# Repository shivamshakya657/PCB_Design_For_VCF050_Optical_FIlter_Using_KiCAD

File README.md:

# PCB_Design-_For_VCF050_Optical_FIlter_Using_KiCAD
In this project, My task is to design PCB for electronics control of Optical Bandpass filter using KiCAD from scratch.

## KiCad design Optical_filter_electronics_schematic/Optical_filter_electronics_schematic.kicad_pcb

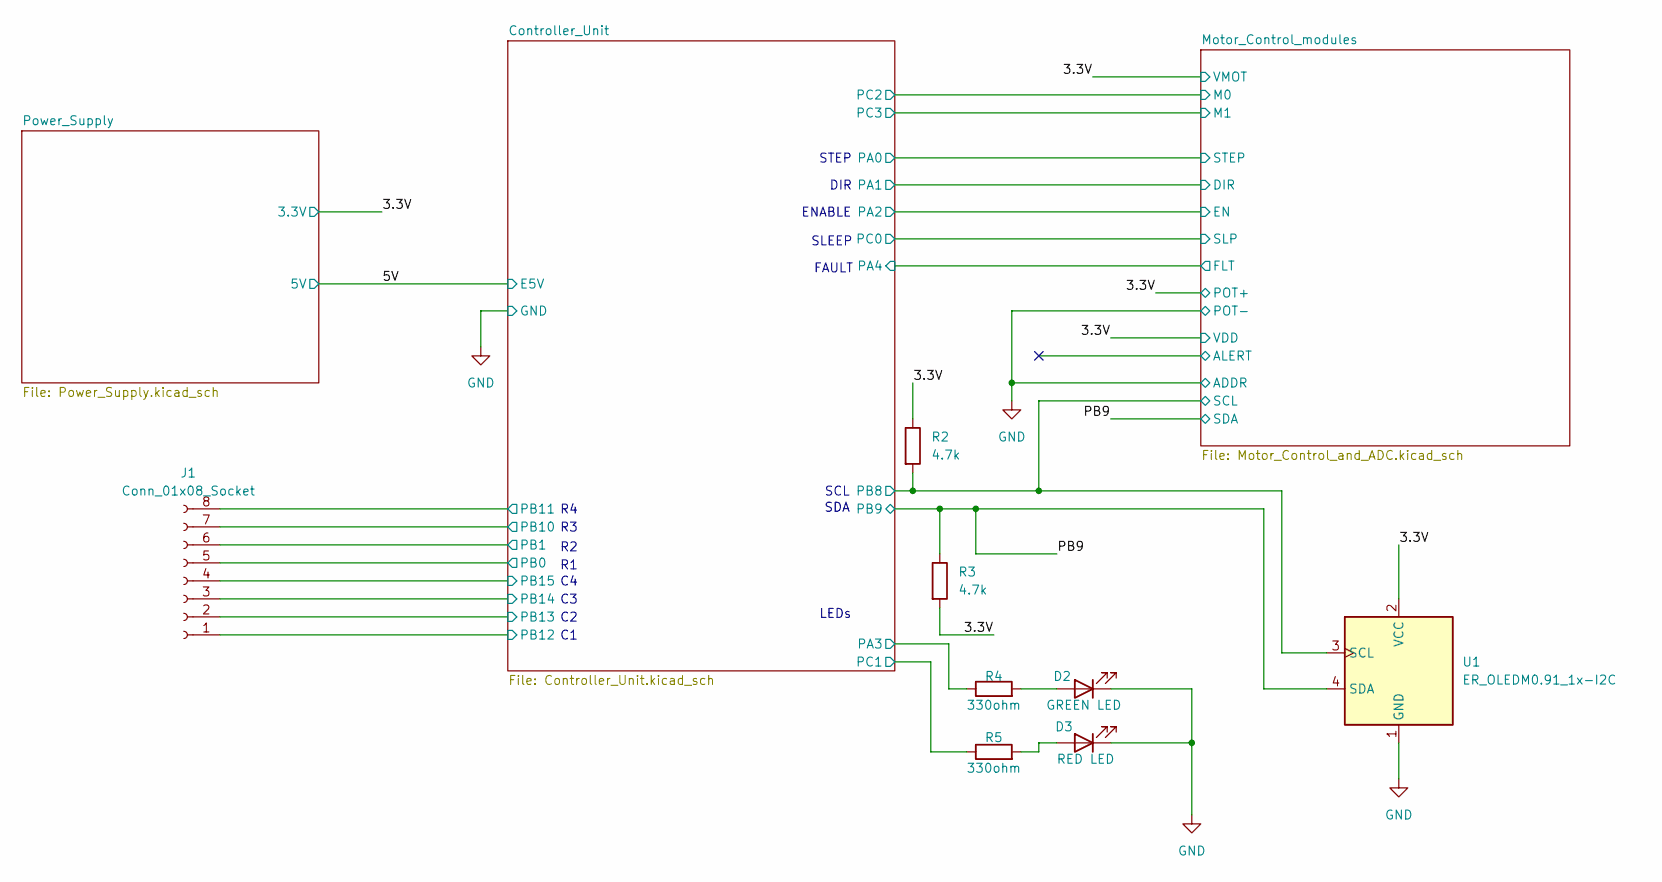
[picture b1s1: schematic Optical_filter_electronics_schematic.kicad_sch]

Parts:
D2: GREEN LED; LED_D5.0mm
D3: RED LED; LED_D5.0mm
J1: Conn_01x08_Socket; Keypad_4x4_footprint
R2, R3: 4.7k; R_0805_2012Metric_Pad1.20x1.40mm_HandSolder
R4, R5: 330ohm; R_0805_2012Metric_Pad1.20x1.40mm_HandSolder
U1: ER_OLEDM0.91_1x-I2C; 128x64OLED_custom_footprint

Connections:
/3.3V: R2.1, R3.2, U1.2 (VCC); also elsewhere on the board
/Controller_Unit/PA3: R4.1; also elsewhere on the board
/Controller_Unit/PB0: J1.5; also elsewhere on the board
/Controller_Unit/PB1: J1.6; also elsewhere on the board
/Controller_Unit/PB8: R2.2, U1.3 (SCL); also elsewhere on the board
/Controller_Unit/PB10: J1.7; also elsewhere on the board
/Controller_Unit/PB11: J1.8; also elsewhere on the board
/Controller_Unit/PB12: J1.1; also elsewhere on the board
/Controller_Unit/PB13: J1.2; also elsewhere on the board
/Controller_Unit/PB14: J1.3; also elsewhere on the board
/Controller_Unit/PB15: J1.4; also elsewhere on the board
/Controller_Unit/PC1: R5.1; also elsewhere on the board
/PB9: R3.1, U1.4 (SDA); also elsewhere on the board
GND: D2.1 (K), D3.1 (K), U1.1 (GND); also elsewhere on the board
unnamed: D2.2 (A), R4.2
unnamed: D3.2 (A), R5.2

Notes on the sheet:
SLEEP
STEP
FAULT
LEDs
ENABLE
SDA
SCL
DIR

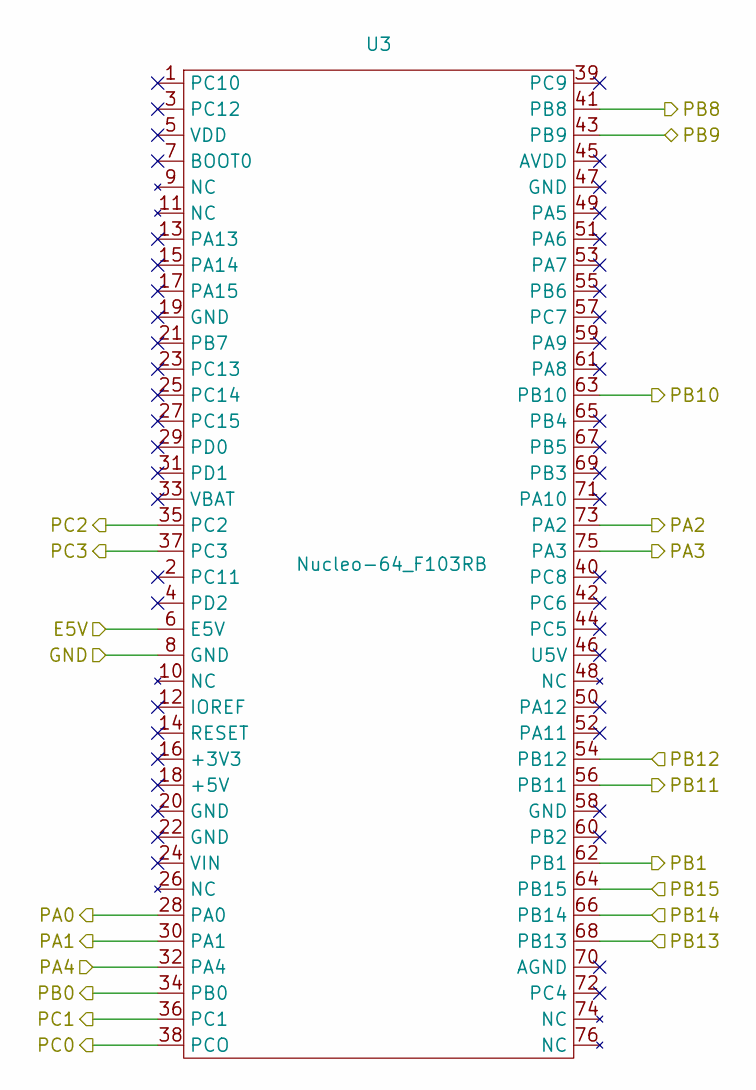
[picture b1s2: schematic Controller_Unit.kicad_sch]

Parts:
U3: Nucleo-64_F103RB; STM32_footprint

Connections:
/5V: U3.6 (E5V); also elsewhere on the board
/Controller_Unit/PA0: U3.28 (PA0); also elsewhere on the board
/Controller_Unit/PA1: U3.30 (PA1); also elsewhere on the board
/Controller_Unit/PA2: U3.73 (PA2); also elsewhere on the board
/Controller_Unit/PA3: U3.75 (PA3); also elsewhere on the board
/Controller_Unit/PA4: U3.32 (PA4); also elsewhere on the board
/Controller_Unit/PB0: U3.34 (PB0); also elsewhere on the board
/Controller_Unit/PB1: U3.62 (PB1); also elsewhere on the board
/Controller_Unit/PB8: U3.41 (PB8); also elsewhere on the board
/Controller_Unit/PB10: U3.63 (PB10); also elsewhere on the board
/Controller_Unit/PB11: U3.56 (PB11); also elsewhere on the board
/Controller_Unit/PB12: U3.54 (PB12); also elsewhere on the board
/Controller_Unit/PB13: U3.68 (PB13); also elsewhere on the board
/Controller_Unit/PB14: U3.66 (PB14); also elsewhere on the board
/Controller_Unit/PB15: U3.64 (PB15); also elsewhere on the board
/Controller_Unit/PC0: U3.38 (PCO); also elsewhere on the board
/Controller_Unit/PC1: U3.36 (PC1); also elsewhere on the board
/Controller_Unit/PC2: U3.35 (PC2); also elsewhere on the board
/Controller_Unit/PC3: U3.37 (PC3); also elsewhere on the board
/PB9: U3.43 (PB9); also elsewhere on the board
GND: U3.8 (GND); also elsewhere on the board

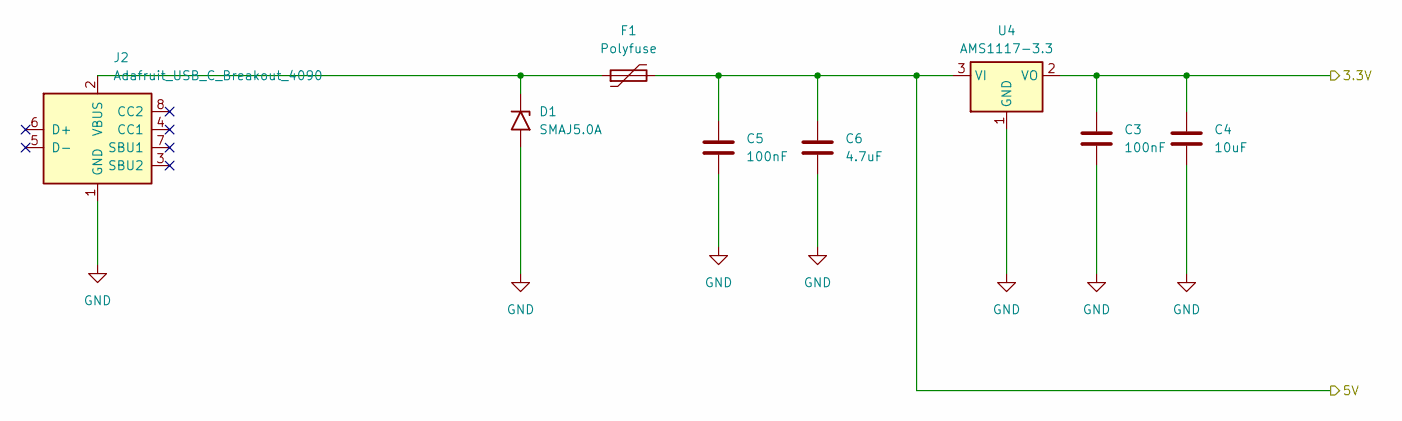
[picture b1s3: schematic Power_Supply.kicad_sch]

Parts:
C3, C5: 100nF; C_0805_2012Metric_Pad1.18x1.45mm_HandSolder
C4: 10uF; C_1206_3216Metric_Pad1.33x1.80mm_HandSolder
C6: 4.7uF; C_1206_3216Metric_Pad1.33x1.80mm_HandSolder
D1: SMAJ5.0A; D_SMA
F1: Polyfuse; Fuse_1812_4532Metric_Pad1.30x3.40mm_HandSolder
J2: Adafruit_USB_C_Breakout_4090
U4: AMS1117-3.3; 3V3_Regulator_Footprint

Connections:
/3.3V: C3.1, C4.1, U4.2 (VO); also elsewhere on the board
/5V: C5.1, C6.1, F1.2, U4.3 (VI); also elsewhere on the board
GND: C3.2, C4.2, C5.2, C6.2, D1.2 (A2), J2.1 (GND), U4.1 (GND); also elsewhere on the board
unnamed: D1.1 (A1), F1.1, J2.2 (VBUS)

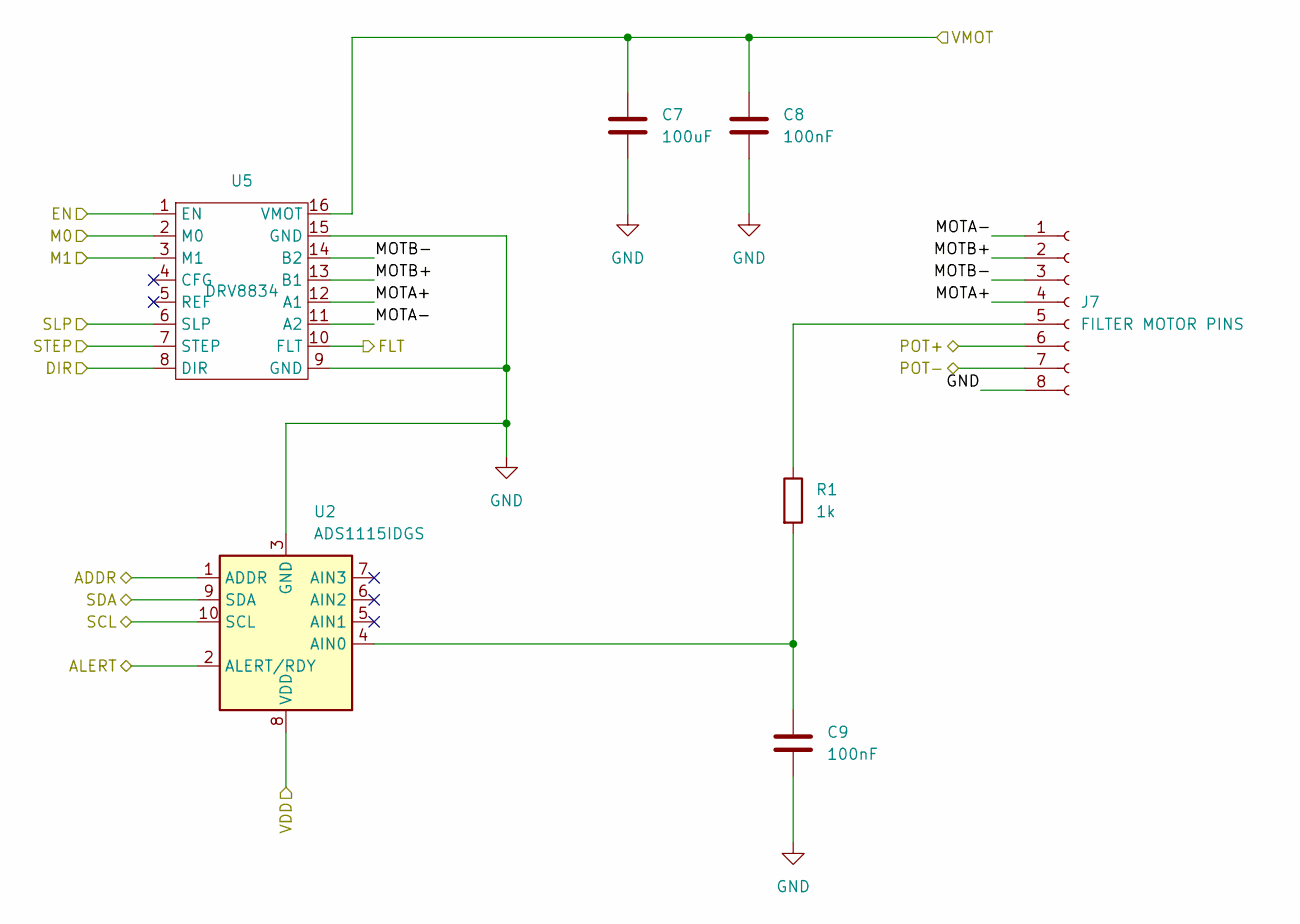
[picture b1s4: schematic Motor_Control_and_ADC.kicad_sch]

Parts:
C7: 100uF; CP_Radial_D6.3mm_P2.50mm
C8, C9: 100nF; C_0805_2012Metric_Pad1.18x1.45mm_HandSolder
J7: FILTER MOTOR PINS; VCF050_Optical_Filter
R1: 1k; R_0805_2012Metric_Pad1.20x1.40mm_HandSolder
U2: ADS1115IDGS; ADC_Module_Footprint
U5: DRV8834; Pololu_Breakout-16_15.2x20.3mm

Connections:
/3.3V: C7.1, C8.1, J7.6, U2.8 (VDD), U5.16 (VMOT); also elsewhere on the board
/Controller_Unit/PA0: U5.7 (STEP); also elsewhere on the board
/Controller_Unit/PA1: U5.8 (DIR); also elsewhere on the board
/Controller_Unit/PA2: U5.1 (EN); also elsewhere on the board
/Controller_Unit/PA4: U5.10 (FLT); also elsewhere on the board
/Controller_Unit/PB8: U2.10 (SCL); also elsewhere on the board
/Controller_Unit/PC0: U5.6 (SLP); also elsewhere on the board
/Controller_Unit/PC2: U5.2 (M0); also elsewhere on the board
/Controller_Unit/PC3: U5.3 (M1); also elsewhere on the board
/Motor_Control_modules/ALERT: U2.2 (ALERT/RDY)
/Motor_Control_modules/MOTA+: J7.4, U5.12 (A1)
/Motor_Control_modules/MOTA-: J7.1, U5.11 (A2)
/Motor_Control_modules/MOTB+: J7.2, U5.13 (B1)
/Motor_Control_modules/MOTB-: J7.3, U5.14 (B2)
/PB9: U2.9 (SDA); also elsewhere on the board
GND: C7.2, C8.2, C9.2, J7.7, J7.8, U2.1 (ADDR), U2.3 (GND), U5.9 (GND), U5.15 (GND); also elsewhere on the board
unnamed: J7.5, R1.1
unnamed: C9.1, R1.2, U2.4 (AIN0)

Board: 2 copper layers, 24 parts (7 on the bottom side), 31 nets, no tracks yet.
